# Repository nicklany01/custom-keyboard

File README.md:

# Custom Keyboard
## Releases
The built program can be found in github actions under the corresponding commit. There will be a file called "fireware.zip" that can be downloaded and flashed to the keyboard.
## Flashing Instructions
1. Connect the keyboard via a USB cable.
2. Double click the reset button on the keyboard (found below the rotary encoder) to enter bootloader mode. The keyboard should show up as a mass storage device on your computer.
3. Copy the "firmware.uf2" file from the downloaded release to the mass storage device to flash the keyboard. The storage device should automatically eject and the keyboard will reboot with the new firmware.
## Local Build Instructions
Source code is built in github actions using the ZMK firmware framework. To build the firmware locally, follow these steps:
1. Clone the ZMK repository using the following command:
```
git clone https://github.com/zmkfirmware/zmk.git
```
2. Set up the Zephyr SDK as described [here](https://docs.zephyrproject.org/3.5.0/develop/getting_started/index.html)
3. From the zmk directory, run the following commands to build the firmware, ensuring to replace "/path/to/this/repo/config" with the path to the config directory in this repository:
```
cd app
# To build the left side:
west build -p -b nice_nano@2.0.0 -- -DSHIELD="chirality_left nice_view_gem" -DZMK_CONFIG=/path/to/this/repo/config

# To build the right side:
west build -p -b nice_nano@2.0.0 -- -DSHIELD="chirality_right nice_view_gem" -DZMK_CONFIG=/path/to/this/repo/config
```
The built firmware file can be found at "/path/to/zmk/app/build/zephyr/zmk.uf2", and can be flashed with the [flash instructions](#flashing-instructions) above, treating "zmk.uf2" as "firmware.uf2".
For more information, see the [ZMK documentation](https://zmk.dev/docs/development/local-toolchain/setup/native) and [Zephyr documentation](https://docs.zephyrproject.org/3.5.0/develop/getting_started/index.html)

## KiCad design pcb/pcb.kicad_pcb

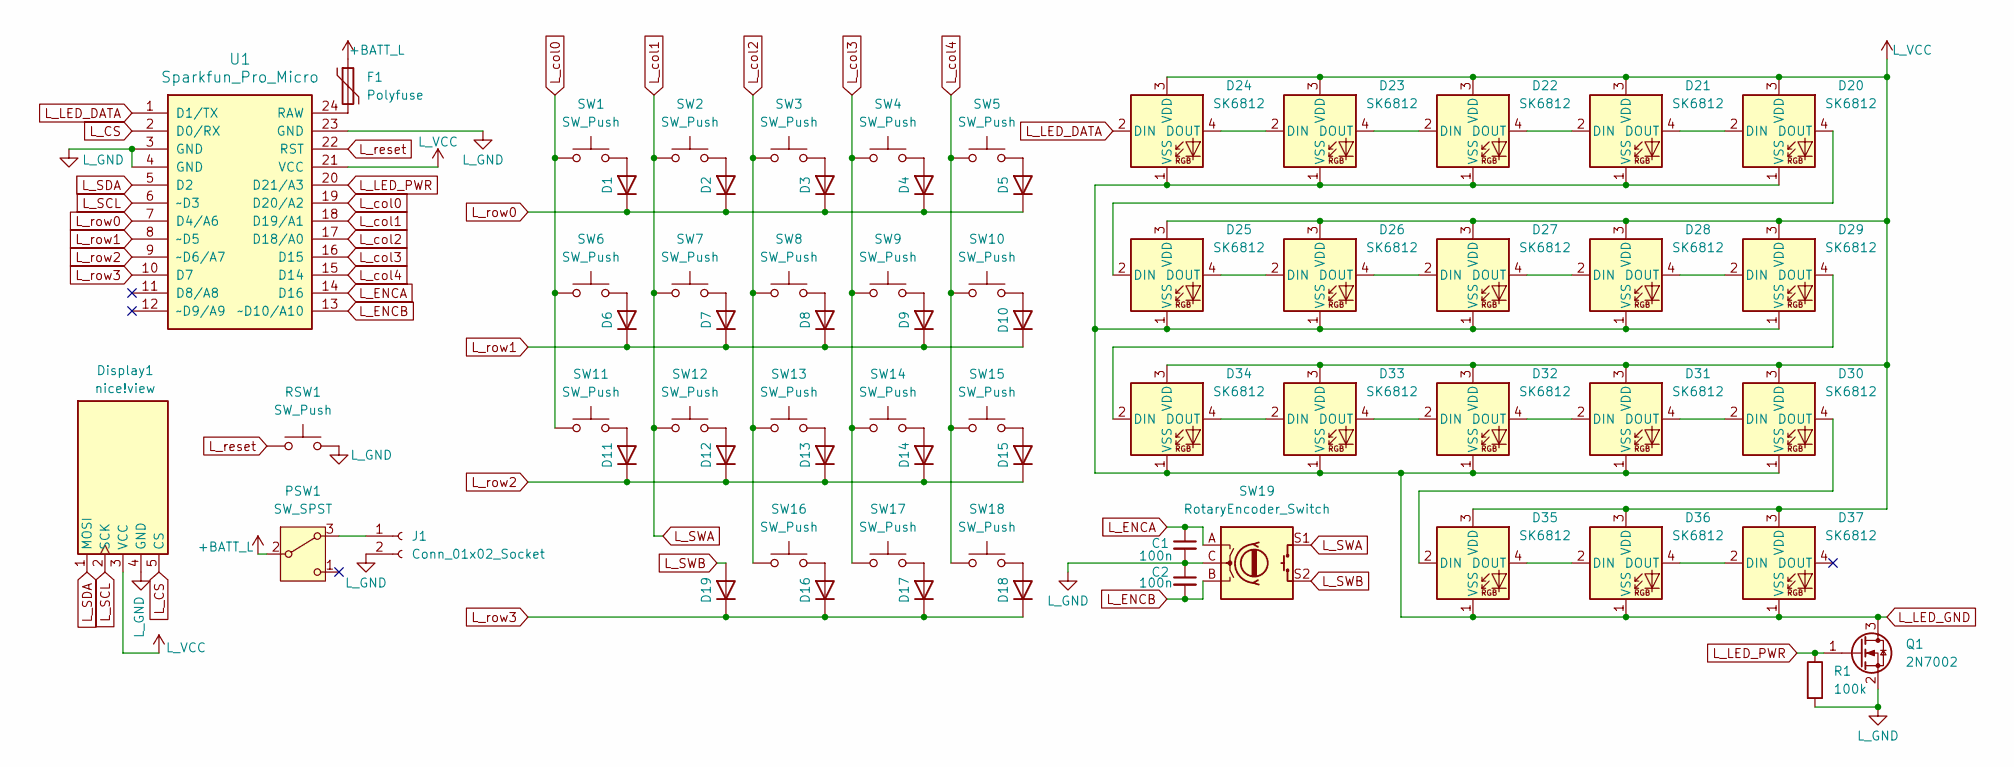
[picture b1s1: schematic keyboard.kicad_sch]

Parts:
C1, C2: 100n; 0805_2012_nonpolarised
D1, D2, D3, D4, D5, D6, D7, D8, D9, D10, D11, D12, D13, D14, D15, D16, D17, D18, D19: 1N4148WT; D_SOD-523
D20, D21, D22, D23, D24, D25, D26, D27, D28, D29, D30, D31, D32, D33, D34, D35, D36, D37: SK6812; SK6812_4020_SIDE_rev2
Display1: nice!view; nice_view
F1: Polyfuse; 0805_2012_nonpolarised
J1: Conn_01x02_Socket; JST_PH_S2B-PH-SM4-TB_1x02-1MP_P2.00mm_Horizontal
PSW1: SW_SPST; SW_SPDT_PCM12
Q1: 2N7002; SOT-23-3
R1: 100k; 0805_2012_nonpolarised
RSW1: SW_Push; SW_SPST_FSMSM
SW1, SW2, SW3, SW4, SW5, SW6, SW7, SW8, SW9, SW10, SW11, SW12, SW13, SW14, SW15, SW16, SW17, SW18: SW_Push; gateron-ks27-hotswap-reversible
SW19: RotaryEncoder_Switch; RotaryEncoder_Alps_EC11E-Switch_Vertical_H20mm
U1: Sparkfun_Pro_Micro

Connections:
+BATT_L: F1.1, PSW1.2 (B)
L_CS: Display1.5 (CS), U1.2 (D0/RX)
L_ENCA: C1.1, SW19.A, U1.14 (D16)
L_ENCB: C2.2, SW19.B, U1.13 (~D10/A10)
L_GND: C1.2, C2.1, Display1.4 (GND), J1.2, Q1.2 (S), R1.2, RSW1.2, SW19.C, U1.3 (GND), U1.4 (GND), U1.23 (GND)
L_LED_DATA: D24.2 (DIN), U1.1 (D1/TX)
L_LED_GND: D20.1 (VSS), D21.1 (VSS), D22.1 (VSS), D23.1 (VSS), D24.1 (VSS), D25.1 (VSS), D26.1 (VSS), D27.1 (VSS), D28.1 (VSS), D29.1 (VSS), D30.1 (VSS), D31.1 (VSS), D32.1 (VSS), D33.1 (VSS), D34.1 (VSS), D35.1 (VSS), D36.1 (VSS), D37.1 (VSS), Q1.3 (D)
L_LED_PWR: Q1.1 (G), R1.1, U1.20 (D21/A3)
L_SCL: Display1.2 (SCK), U1.6 (~D3)
L_SDA: Display1.1 (MOSI), U1.5 (D2)
L_SWA: SW2.1, SW7.1, SW12.1, SW19.S1, U1.18 (D19/A1)
L_SWB: D19.2 (A), SW19.S2
L_VCC: D20.3 (VDD), D21.3 (VDD), D22.3 (VDD), D23.3 (VDD), D24.3 (VDD), D25.3 (VDD), D26.3 (VDD), D27.3 (VDD), D28.3 (VDD), D29.3 (VDD), D30.3 (VDD), D31.3 (VDD), D32.3 (VDD), D33.3 (VDD), D34.3 (VDD), D35.3 (VDD), D36.3 (VDD), D37.3 (VDD), Display1.3 (VCC), U1.21 (VCC)
L_col0: SW1.1, SW6.1, SW11.1, U1.19 (D20/A2)
L_col2: SW3.1, SW8.1, SW13.1, SW16.1, U1.17 (D18/A0)
L_col3: SW4.1, SW9.1, SW14.1, SW17.1, U1.16 (D15)
L_col4: SW5.1, SW10.1, SW15.1, SW18.1, U1.15 (D14)
L_reset: RSW1.1, U1.22 (RST)
L_row0: D1.1 (K), D2.1 (K), D3.1 (K), D4.1 (K), D5.1 (K), U1.7 (D4/A6)
L_row1: D6.1 (K), D7.1 (K), D8.1 (K), D9.1 (K), D10.1 (K), U1.8 (~D5)
L_row2: D11.1 (K), D12.1 (K), D13.1 (K), D14.1 (K), D15.1 (K), U1.9 (~D6/A7)
L_row3: D16.1 (K), D17.1 (K), D18.1 (K), D19.1 (K), U1.10 (D7)
unnamed: D1.2 (A), SW1.2
unnamed: D2.2 (A), SW2.2
unnamed: D3.2 (A), SW3.2
unnamed: D4.2 (A), SW4.2
unnamed: D5.2 (A), SW5.2
unnamed: D6.2 (A), SW6.2
unnamed: D7.2 (A), SW7.2
unnamed: D8.2 (A), SW8.2
unnamed: D9.2 (A), SW9.2
unnamed: D10.2 (A), SW10.2
unnamed: D11.2 (A), SW11.2
unnamed: D12.2 (A), SW12.2
unnamed: D13.2 (A), SW13.2
unnamed: D14.2 (A), SW14.2
unnamed: D15.2 (A), SW15.2
unnamed: D16.2 (A), SW16.2
unnamed: D17.2 (A), SW17.2
unnamed: D18.2 (A), SW18.2
unnamed: D20.2 (DIN), D21.4 (DOUT)
unnamed: D20.4 (DOUT), D25.2 (DIN)
unnamed: D21.2 (DIN), D22.4 (DOUT)
unnamed: D22.2 (DIN), D23.4 (DOUT)
unnamed: D23.2 (DIN), D24.4 (DOUT)
unnamed: D25.4 (DOUT), D26.2 (DIN)
unnamed: D26.4 (DOUT), D27.2 (DIN)
unnamed: D27.4 (DOUT), D28.2 (DIN)
unnamed: D28.4 (DOUT), D29.2 (DIN)
unnamed: D29.4 (DOUT), D34.2 (DIN)
unnamed: D30.2 (DIN), D31.4 (DOUT)
unnamed: D30.4 (DOUT), D35.2 (DIN)
unnamed: D31.2 (DIN), D32.4 (DOUT)
unnamed: D32.2 (DIN), D33.4 (DOUT)
unnamed: D33.2 (DIN), D34.4 (DOUT)
unnamed: D35.4 (DOUT), D36.2 (DIN)
unnamed: D36.4 (DOUT), D37.2 (DIN)
unnamed: J1.1, PSW1.3 (A)
unnamed: F1.2, U1.24 (RAW)

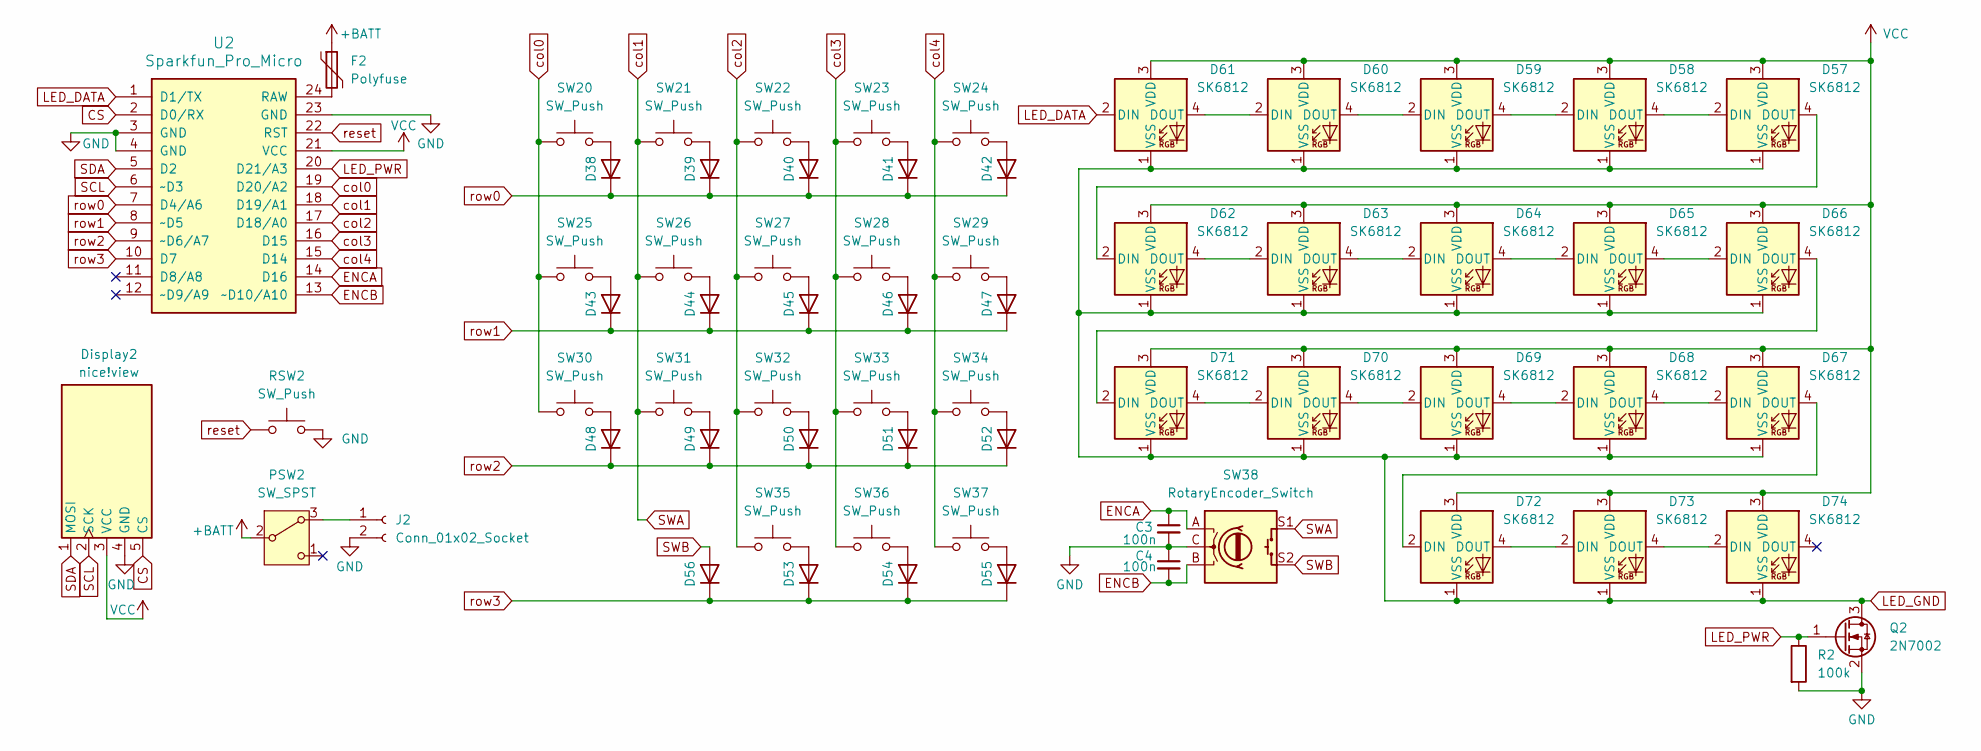
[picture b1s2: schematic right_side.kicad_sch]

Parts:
C3, C4: 100n; 0805_2012_nonpolarised
D38, D39, D40, D41, D42, D43, D44, D45, D46, D47, D48, D49, D50, D51, D52, D53, D54, D55, D56: 1N4148WT; D_SOD-523
D57, D58, D59, D60, D61, D62, D63, D64, D65, D66, D67, D68, D69, D70, D71, D72, D73, D74: SK6812; SK6812_4020_SIDE_rev2
Display2: nice!view; nice_view
F2: Polyfuse; 0805_2012_nonpolarised
J2: Conn_01x02_Socket; JST_PH_S2B-PH-SM4-TB_1x02-1MP_P2.00mm_Horizontal
PSW2: SW_SPST; SW_SPDT_PCM12
Q2: 2N7002; SOT-23-3
R2: 100k; 0805_2012_nonpolarised
RSW2: SW_Push; SW_SPST_FSMSM
SW20, SW21, SW22, SW23, SW24, SW25, SW26, SW27, SW28, SW29, SW30, SW31, SW32, SW33, SW34, SW35, SW36, SW37: SW_Push; gateron-ks27-hotswap-reversible
SW38: RotaryEncoder_Switch; RotaryEncoder_Alps_EC11E-Switch_Vertical_H20mm
U2: Sparkfun_Pro_Micro

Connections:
+BATT: F2.1, PSW2.2 (B)
CS: Display2.5 (CS), U2.2 (D0/RX)
ENCA: C3.1, SW38.A, U2.14 (D16)
ENCB: C4.2, SW38.B, U2.13 (~D10/A10)
GND: C3.2, C4.1, Display2.4 (GND), J2.2, Q2.2 (S), R2.2, RSW2.2, SW38.C, U2.3 (GND), U2.4 (GND), U2.23 (GND)
LED_DATA: D61.2 (DIN), U2.1 (D1/TX)
LED_GND: D57.1 (VSS), D58.1 (VSS), D59.1 (VSS), D60.1 (VSS), D61.1 (VSS), D62.1 (VSS), D63.1 (VSS), D64.1 (VSS), D65.1 (VSS), D66.1 (VSS), D67.1 (VSS), D68.1 (VSS), D69.1 (VSS), D70.1 (VSS), D71.1 (VSS), D72.1 (VSS), D73.1 (VSS), D74.1 (VSS), Q2.3 (D)
LED_PWR: Q2.1 (G), R2.1, U2.20 (D21/A3)
unnamed: D38.2 (A), SW20.2
unnamed: D39.2 (A), SW21.2
unnamed: D40.2 (A), SW22.2
unnamed: D41.2 (A), SW23.2
unnamed: D42.2 (A), SW24.2
unnamed: D43.2 (A), SW25.2
unnamed: D44.2 (A), SW26.2
unnamed: D45.2 (A), SW27.2
unnamed: D46.2 (A), SW28.2
unnamed: D47.2 (A), SW29.2
unnamed: D48.2 (A), SW30.2
unnamed: D49.2 (A), SW31.2
unnamed: D50.2 (A), SW32.2
unnamed: D51.2 (A), SW33.2
unnamed: D52.2 (A), SW34.2
unnamed: D53.2 (A), SW35.2
unnamed: D54.2 (A), SW36.2
unnamed: D55.2 (A), SW37.2
unnamed: D57.2 (DIN), D58.4 (DOUT)
unnamed: D57.4 (DOUT), D62.2 (DIN)
unnamed: D58.2 (DIN), D59.4 (DOUT)
unnamed: D59.2 (DIN), D60.4 (DOUT)
unnamed: D60.2 (DIN), D61.4 (DOUT)
unnamed: D62.4 (DOUT), D63.2 (DIN)
unnamed: D63.4 (DOUT), D64.2 (DIN)
unnamed: D64.4 (DOUT), D65.2 (DIN)
unnamed: D65.4 (DOUT), D66.2 (DIN)
unnamed: D66.4 (DOUT), D71.2 (DIN)
unnamed: D67.2 (DIN), D68.4 (DOUT)
unnamed: D67.4 (DOUT), D72.2 (DIN)
unnamed: D68.2 (DIN), D69.4 (DOUT)
unnamed: D69.2 (DIN), D70.4 (DOUT)
unnamed: D70.2 (DIN), D71.4 (DOUT)
unnamed: D72.4 (DOUT), D73.2 (DIN)
unnamed: D73.4 (DOUT), D74.2 (DIN)
unnamed: J2.1, PSW2.3 (A)
unnamed: F2.2, U2.24 (RAW)
SCL: Display2.2 (SCK), U2.6 (~D3)
SDA: Display2.1 (MOSI), U2.5 (D2)
SWA: SW21.1, SW26.1, SW31.1, SW38.S1, U2.18 (D19/A1)
SWB: D56.2 (A), SW38.S2
VCC: D57.3 (VDD), D58.3 (VDD), D59.3 (VDD), D60.3 (VDD), D61.3 (VDD), D62.3 (VDD), D63.3 (VDD), D64.3 (VDD), D65.3 (VDD), D66.3 (VDD), D67.3 (VDD), D68.3 (VDD), D69.3 (VDD), D70.3 (VDD), D71.3 (VDD), D72.3 (VDD), D73.3 (VDD), D74.3 (VDD), Display2.3 (VCC), U2.21 (VCC)
col0: SW20.1, SW25.1, SW30.1, U2.19 (D20/A2)
col2: SW22.1, SW27.1, SW32.1, SW35.1, U2.17 (D18/A0)
col3: SW23.1, SW28.1, SW33.1, SW36.1, U2.16 (D15)
col4: SW24.1, SW29.1, SW34.1, SW37.1, U2.15 (D14)
reset: RSW2.1, U2.22 (RST)
row0: D38.1 (K), D39.1 (K), D40.1 (K), D41.1 (K), D42.1 (K), U2.7 (D4/A6)
row1: D43.1 (K), D44.1 (K), D45.1 (K), D46.1 (K), D47.1 (K), U2.8 (~D5)
row2: D48.1 (K), D49.1 (K), D50.1 (K), D51.1 (K), D52.1 (K), U2.9 (~D6/A7)
row3: D53.1 (K), D54.1 (K), D55.1 (K), D56.1 (K), U2.10 (D7)

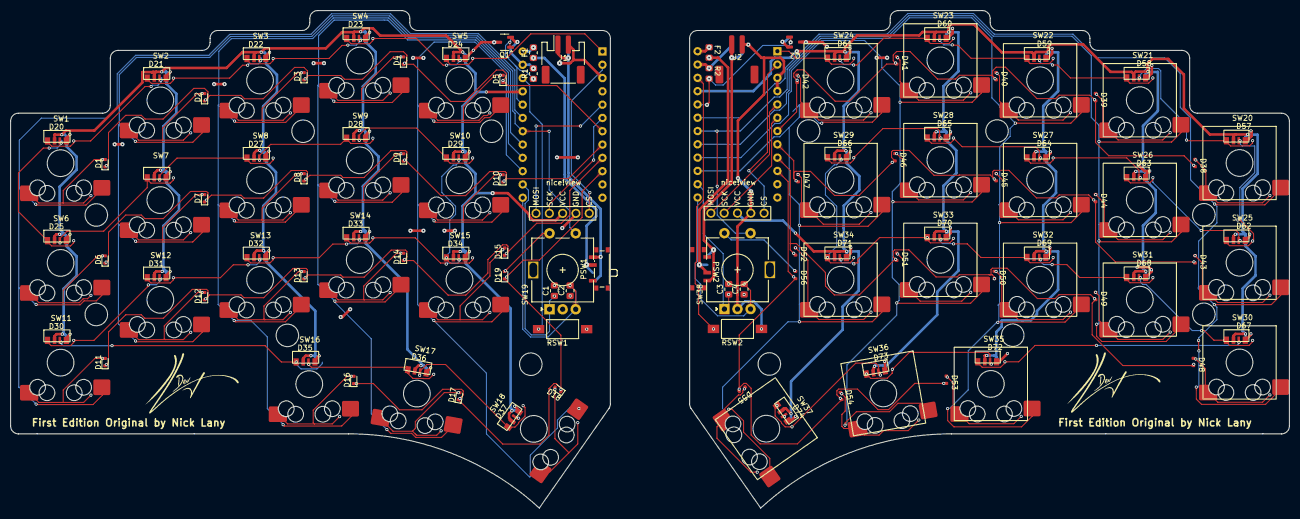
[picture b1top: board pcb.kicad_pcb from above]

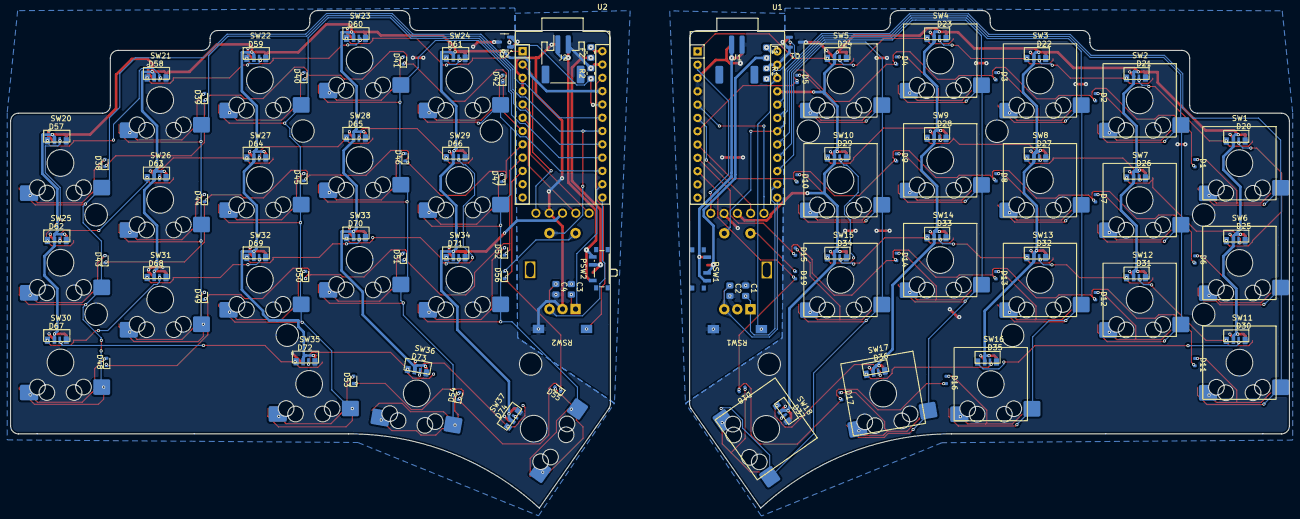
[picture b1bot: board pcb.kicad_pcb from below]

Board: 2 copper layers, 244.3 x 95.0 mm, 132 parts (62 on the bottom side), 118 nets.

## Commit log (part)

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2025-10-30 Initial User Config.
2025-10-30 Add PCB
2025-10-30 Add Readme
2025-12-09 Add basic keyboard layout
2025-12-09 Remove old schematics
2025-12-10 Fix issue connecting central control node (left) to peripheral node (right)
2025-12-10 Revert "Remove old schematics"
    This reverts commit 279f44eda0d01da2331cf1d736d6b6c595c70e90.
    I fucked up. These schematics were part of the hierarchical schematics
    and are needed.
2025-12-11 Add nice_view screen capability
2025-12-11 Add rotary encoder functionality
2025-12-31 Add case files and documentation
2025-12-31 Add finished top plate
    Modified pcb layers to be exportable.
    Added export script to export svg files
    Completed top plate design
2026-01-01 Fix top plate screw hole size
2026-01-01 Add cutout for dev board on top plate
2026-01-01 Add basic case shape
2026-05-14 Fix memory persistence and rgb issues
2026-05-16 Make case tilt, walls and battery compartment
2026-05-16 Adjust dimensions to match physical keyboard, and add battery resting platform
2026-05-16 Modify base to be solid instead of hollow, add visualization option
2026-05-16 Add wiring cutout to allow battery to connect to pcb
2026-05-16 Add chamfer
2026-05-19 Add offset around case for smoother fit, add charger and switch cutouts
2026-05-20 Add logo
2026-05-22 Add text
2026-05-23 Add mirroring of text to right side
2026-05-30 Add adjustments to tent angle and switch cutout
2026-05-30 add top screen case pcb outlines
2026-05-31 add top case part to fit in top
2026-05-31 Add clearances for slotting parts
2026-05-31 Remove Aider from gitignore
2026-05-31 fix github actions
2026-05-31 readd extra wall bit to inside of top wall
2026-05-31 adjust screw holes and battery cutout
2026-06-14 change stl export to step file
2026-06-15 change direction of right rotary encoder, add mouse
2026-06-18 change zmk rgb leds to sleep after 15 mins even when plugged in
